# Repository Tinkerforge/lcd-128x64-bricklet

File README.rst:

LCD 128x64 Bricklet
===================

This repository contains the firmware source code and the hardware design
files. The documentation generator configs can be found at
https://github.com/Tinkerforge/generators

Repository Content
------------------

software/:
 * examples/: Examples for all supported languages
 * build/: Compiled files
 * src/: Source code of firmware
 * Makefile: Makefile to build project

hardware/:
 * Contains KiCad project files and additionally schematics as PDF

datasheets/:
 * Contains datasheets for sensors and complex ICs that are used

Hardware
--------

The hardware is designed with the open source EDA Suite KiCad
(http://www.kicad.org). Before you are able to open the files,
you have to install the Tinkerforge kicad-libraries
(https://github.com/Tinkerforge/kicad-libraries). You can either clone
them directly in hardware/ or clone them in a separate folder and
symlink them into hardware/
(ln -s kicad_path/kicad-libraries project_path/hardware). After that you
can open the .pro file in hardware/ with KiCad and from there view and
modify the schematics and the PCB layout.

Software
--------

If you want to do your own Brick/Bricklet firmware development we highly
recommend that you use our build environment setup script and read the
tutorial (https://www.tinkerforge.com/en/doc/Tutorials/Tutorial_Build_Environment/Tutorial.html).

To compile the C code we recommend you to install the newest GNU Arm Embedded
Toolchain (https://launchpad.net/gcc-arm-embedded/+download).
You also need to install bricklib2 (https://github.com/Tinkerforge/bricklib2).

You can either clone it directly in software/src/ or clone it in a
separate folder and symlink it into software/src/
(ln -s bricklib_path/bricklib2 project_path/software/src/). Finally make sure to
have CMake installed (http://www.cmake.org/cmake/resources/software.html).

After that you can build the firmware by invoking make in software/.
The firmware (.zbin) can then be found in software/build/ and uploaded
with brickv (click button "Flashing" on start screen).

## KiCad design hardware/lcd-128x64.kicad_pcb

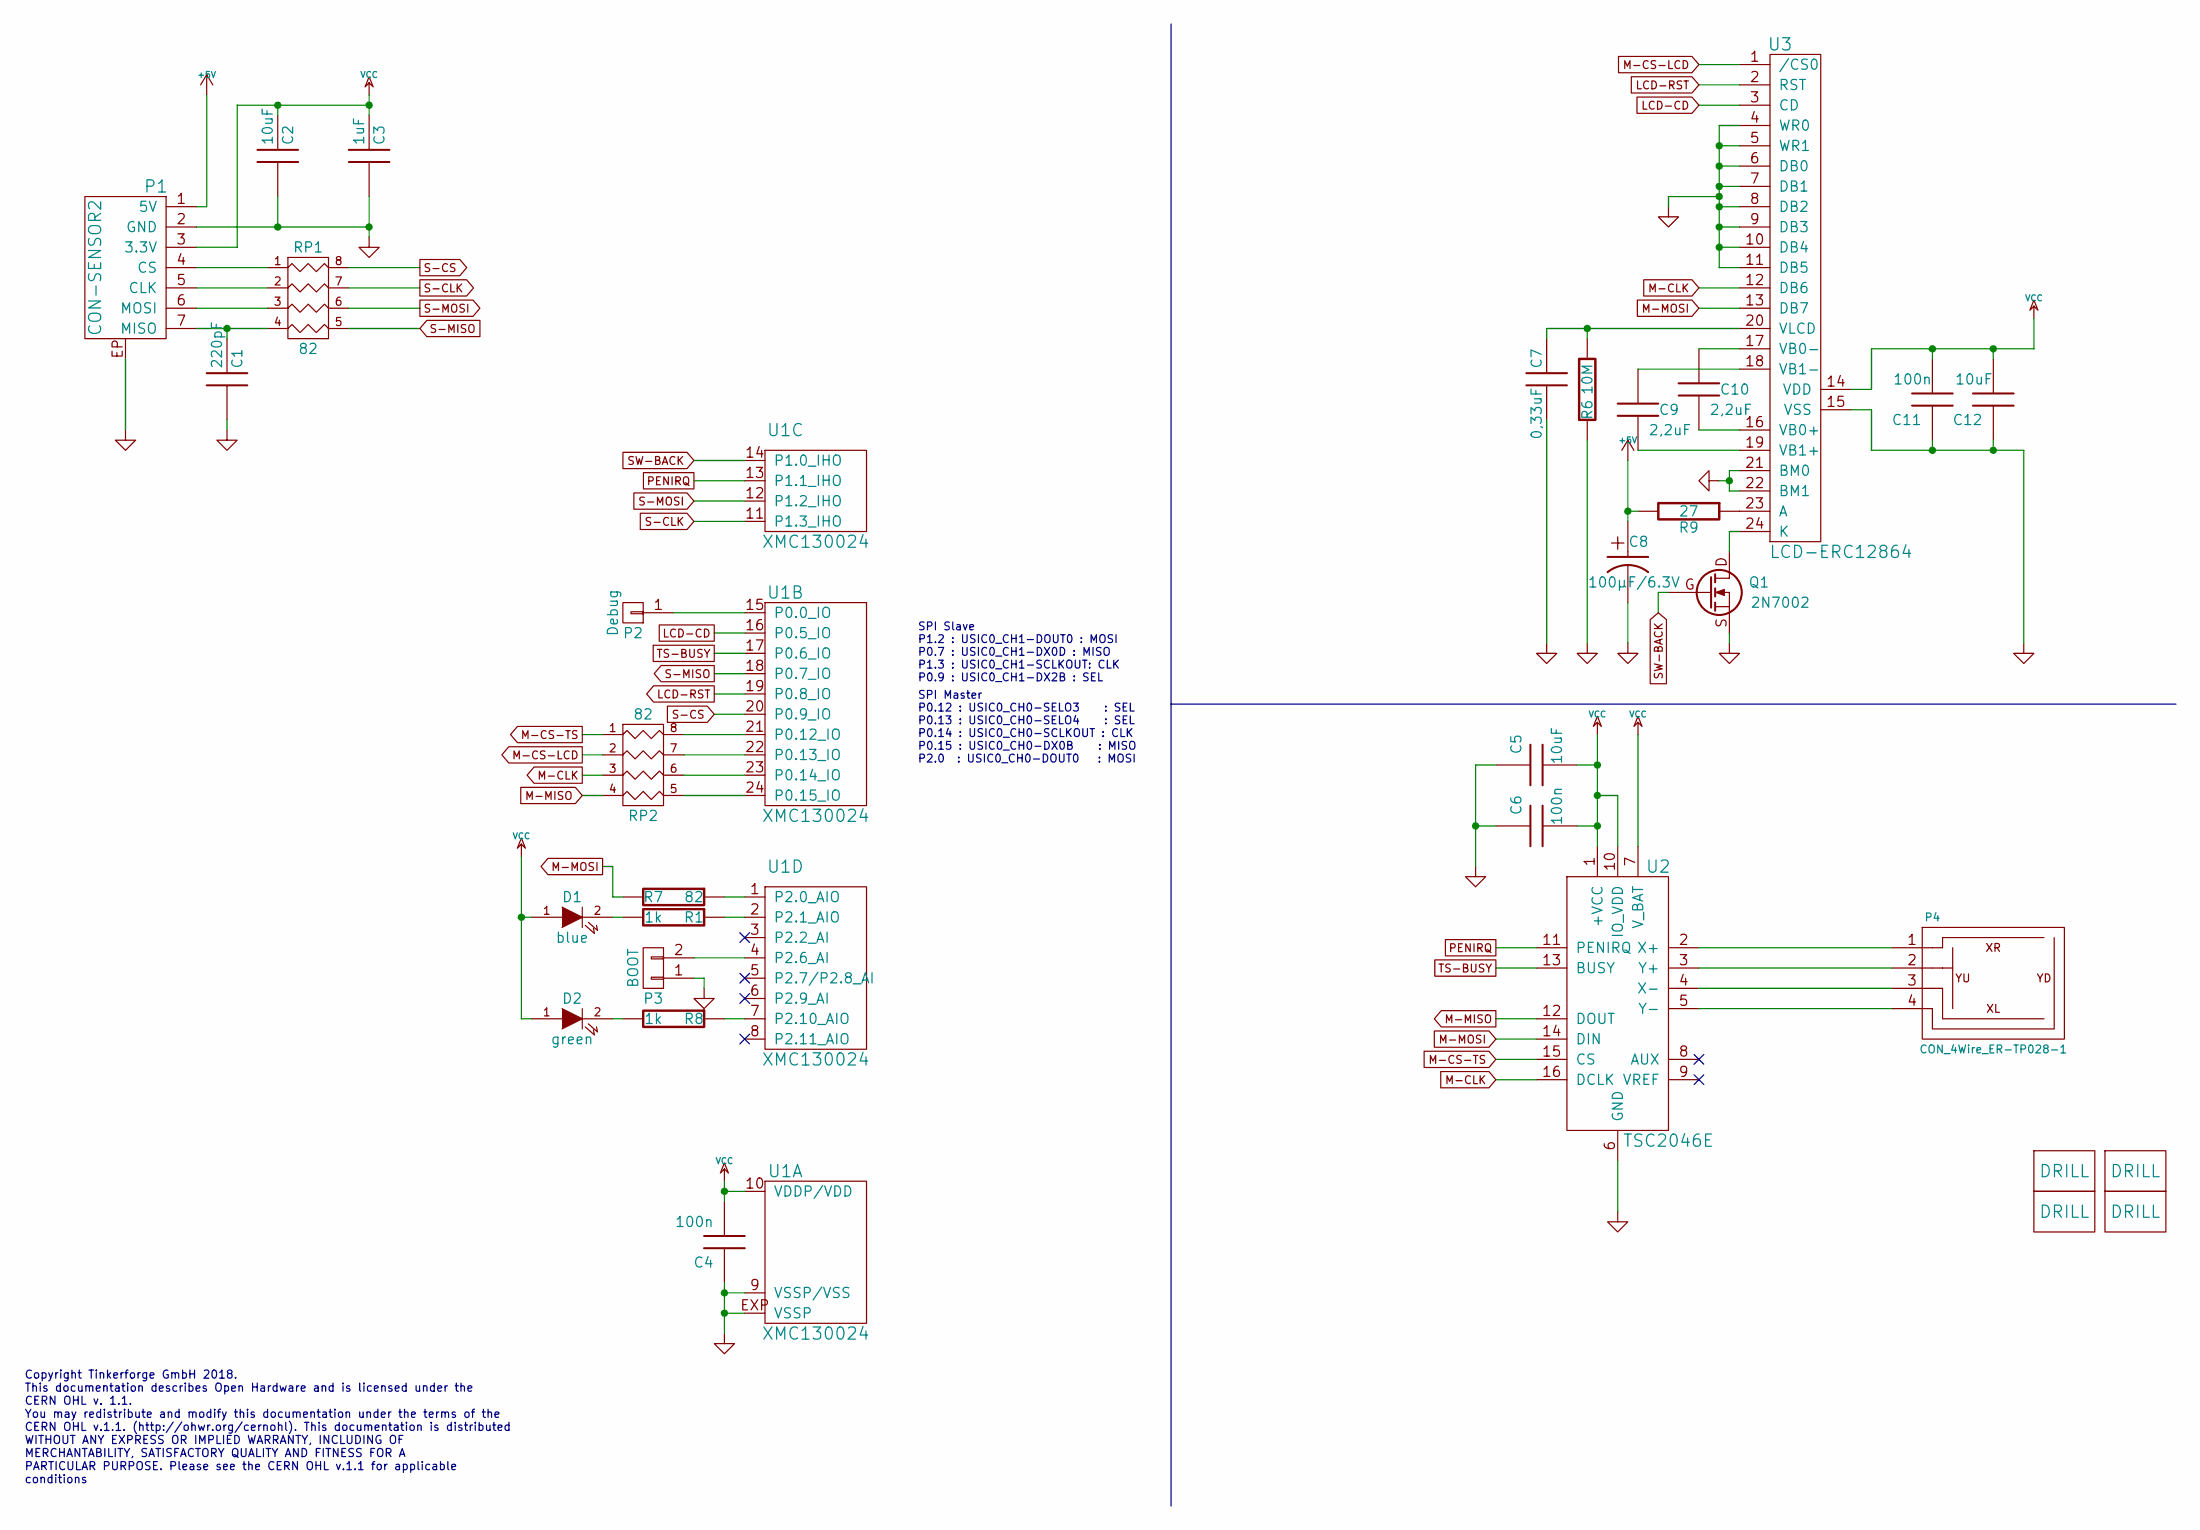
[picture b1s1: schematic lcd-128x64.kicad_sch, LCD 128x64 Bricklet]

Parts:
C1: 220pF; C0402F
C2, C5, C12: 10uF; C0805
C3: 1uF; C0603F
C4, C6, C11: 100n; C0603F
C7: 0,33uF; R0603F
C8: 100µF/6.3V; 3528-21
C9, C10: 2,2uF; C0603F
D1: blue; D0603E
D2: green; D0603E
P1: CON-SENSOR2
P2: Debug; DEBUG_PAD
P3: BOOT; SolderJumper
P4: CON_4Wire_ER-TP028-1; ER-CON04HB-2
Q1: 2N7002; SOT23GDS
R1, R8: 1k; R0603F
R6: 10M; R0603F
R7: 82; R0402F
R9: 27; R1206
RP1, RP2: 82; 4X0402
U1: XMC130024; QFN24-4x4mm-0.5mm
U2: TSC2046E; TSSOP16
U3: LCD-ERC12864; ERC12864-655_128x64
U4, U5, U6, U7: DRILL; DRILL_NP

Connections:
+5V: C8.1, P1.1 (5V), R9.2
GND: C1.2, C2.2, C3.2, C4.1, C5.1, C6.1, C7.2, C8.2, C11.1, C12.1, P1.2 (GND), P1.EP, P3.1, Q1.S, R6.2, U1.9 (VSSP/VSS), U1.EXP (VSSP), U2.6 (GND), U3.4 (WR0), U3.5 (WR1), U3.6 (DB0), U3.7 (DB1), U3.8 (DB2), U3.9 (DB3), U3.10 (DB4), U3.11 (DB5), U3.15 (VSS), U3.21 (BM0), U3.22 (BM1)
LCD-CD: U1.16 (P0.5_IO), U3.3 (CD)
LCD-RST: U1.19 (P0.8_IO), U3.2 (RST)
M-CLK: RP2.3, U2.16 (DCLK), U3.12 (DB6)
M-CS-LCD: RP2.2, U3.1 (/CS0)
M-CS-TS: RP2.1, U2.15 (CS)
M-MISO: RP2.4, U2.12 (DOUT)
M-MOSI: R7.2, U2.14 (DIN), U3.13 (DB7)
unnamed: C1.1, P1.7 (MISO), RP1.4
unnamed: C7.1, R6.1, U3.20 (VLCD)
unnamed: C9.1, U3.18 (VB1-)
unnamed: C9.2, U3.19 (VB1+)
unnamed: C10.1, U3.17 (VB0-)
unnamed: C10.2, U3.16 (VB0+)
unnamed: D1.2 (K), R1.2
unnamed: D2.2 (K), R8.2
unnamed: P1.4 (CS), RP1.1
unnamed: P1.5 (CLK), RP1.2
unnamed: P1.6 (MOSI), RP1.3
unnamed: P2.1, U1.15 (P0.0_IO)
unnamed: P3.2, U1.4 (P2.6_AI)
unnamed: P4.1, U2.2 (X+)
unnamed: P4.2, U2.3 (Y+)
unnamed: P4.3, U2.4 (X-)
unnamed: P4.4, U2.5 (Y-)
unnamed: Q1.D, U3.24 (K)
unnamed: R1.1, U1.2 (P2.1_AIO)
unnamed: R7.1, U1.1 (P2.0_AIO)
unnamed: R8.1, U1.7 (P2.10_AIO)
unnamed: R9.1, U3.23 (A)
unnamed: RP2.5 (R4), U1.24 (P0.15_IO)
unnamed: RP2.6 (R3), U1.23 (P0.14_IO)
unnamed: RP2.7 (R2), U1.22 (P0.13_IO)
unnamed: RP2.8 (R1), U1.21 (P0.12_IO)
PENIRQ: U1.13 (P1.1_IHO), U2.11 (PENIRQ)
S-CLK: RP1.7 (R2), U1.11 (P1.3_IHO)
S-CS: RP1.8 (R1), U1.20 (P0.9_IO)
S-MISO: RP1.5 (R4), U1.18 (P0.7_IO)
S-MOSI: RP1.6 (R3), U1.12 (P1.2_IHO)
SW-BACK: Q1.G, U1.14 (P1.0_IHO)
TS-BUSY: U1.17 (P0.6_IO), U2.13 (BUSY)
VCC: C2.1, C3.1, C4.2, C5.2, C6.2, C11.2, C12.2, D1.1 (A), D2.1 (A), P1.3 (3.3V), U1.10 (VDDP/VDD), U2.1 (+VCC), U2.7 (V_BAT), U2.10 (IO_VDD), U3.14 (VDD)

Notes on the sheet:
SPI Slave P1.2 : USIC0_CH1-DOUT0 : MOSI P0.7 : USIC0_CH1-DX0D : MISO P1.3 : USIC0_CH1-SCLKOUT: CLK P0.9 : USIC0_CH1-DX2B : SEL
SPI Master P0.12 : USIC0_CH0-SELO3 : SEL P0.13 : USIC0_CH0-SELO4 : SEL P0.14 : USIC0_CH0-SCLKOUT : CLK P0.15 : USIC0_CH0-DX0B : MISO P2.0 : USIC0_CH0-DOUT0 : MOSI
Copyright Tinkerforge GmbH 2018. This documentation describes Open Hardware and is licensed under the CERN OHL v. 1.1. You may redistribute and modify this documentation under the terms of the CERN OHL v.1.1. (http://ohwr.org/cernohl). This documentation is distributed WITHOUT ANY EXPRESS OR IMPLIE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

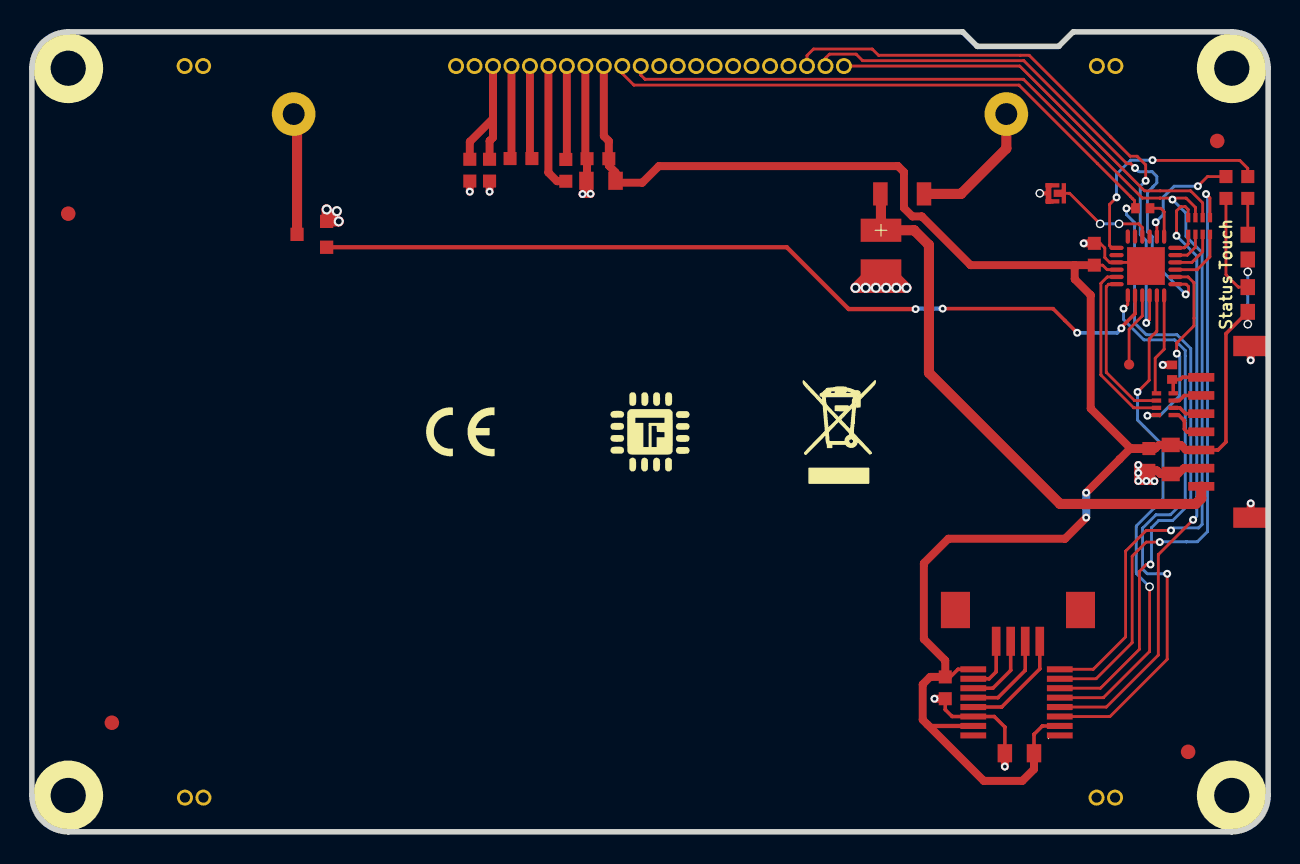
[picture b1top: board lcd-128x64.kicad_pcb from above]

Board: 2 copper layers, 85.0 x 55.0 mm, 39 parts (1 on the bottom side), 43 nets.

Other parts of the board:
Fiducial_Mark: VAL**; Fiducial_Mark
Fiducial_Mark#2, Fiducial_Mark#3, Fiducial_Mark#4: VAL**; Fiducial_Mark
VAL: WEEE_7mm
VAL#2: CE_5mm

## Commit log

2017-12-04 Add datasheets
2017-12-04 Add initial schematic
2017-12-04 Add touch screen controller
2017-12-04 Add connection between touchscreen and XMC
2017-12-04 add interfacing document
2017-12-04 * change 0402 parts to 0603 * change SPI slave an master interfaces
2017-12-05 Annotate components and minor adjustments
2017-12-05 Assign footprints
2017-12-05 Initial PCB
2017-12-05 Fix footprints C11, U2
2017-12-06 add drawing of touchscreen cable
2017-12-07 Change SPI pins, change LCD interface to write-only
2017-12-07 Change pins from debug and boot pads
2017-12-07 Fix last commit
2017-12-07 Complete routing
2017-12-07 add fiducials, destroy layout
2017-12-07 Add status LED for touch
2017-12-07 Change footprint from 0603F to 0805: C5
2017-12-07 Recover routing
2017-12-07 some small layout improvements
2018-01-04 Change pins P1.3 with P0.8
2018-01-04 Resize touchscreen cable through hole
2018-01-08 Fix filled zone
2018-01-08 Change 2017 to 2018
2018-01-22 Bigger holes for LCD
2018-01-25 Change SPI pins because of flashing failure
2018-02-12 display has to be connected to MOSI (not MISO)
2018-02-12 change lcd128 footprint
2018-02-20 Add .gitignore
2018-02-20 Cleanup KiCad libraries config
    Ensure LibDir=kicad-libraries and LibName1=tinkerforge.
    Remove special library.
2018-03-27 Connect LCD backlight to 5v
2018-03-27 Add firmware
2018-03-27 Add missing automatic draw check
2018-03-28 add vscode directory
2018-03-28 Use current max line/position numbers
2018-03-28 Rename column/row to x/y in API
2018-03-28 Add age to touch/gesture callbacks
2018-04-04 Add support for ReadPixels API
2018-04-04 Add new layout (tbc)
2018-04-04 Add simple tests
2018-04-06 Add new layout
2018-04-06 Minor layout adjustments
2018-05-07 hardware changes
    * move touchscreen connector +2mm
    * remove unneccssary resistors
    * move led positions and texts
    * swap led connections
2018-05-11 Rename files
2018-06-06 fix text, set origin
2018-06-18 Fix libraries and footprint
2018-06-28 Fix readme
2018-07-11 Add Makefile with docker support
2018-07-11 Remove obsolete generate_makefile scripts
2018-07-11 Update directory structure and build instructions
2018-07-31 Add 3d model (*.FCStd & *.step)
2018-07-31 Add PDF schematic
2018-09-06 Add font render script
2018-09-10 Use dame coordinate system for touch as for LCD
2018-09-10 Better defaults for contrast and backlight
2018-09-10 Add examples
    LabVIEW example missing.
2018-09-11 Add pixel matrix and scribble example for C
2018-09-11 Add comment with compile parameters
2018-09-11 Add pixel matrix example for Delphi
2018-09-12 Add pixel matrix and scribble examples for java
2018-09-12 Add pixel matrix and scribble example for C#
2018-09-12 Add pixel matrix and scribble examples for JavaScript
2018-09-12 fix c+p error
2018-09-12 Add pixel matrix example for MATLAB/Octave
2018-09-12 Add pixel matrix and scribble example for perl
2018-09-12 Add pixel matrix and scribble example for PHP
2018-09-12 Add pixel matrix and scribble examples for Ruby
2018-09-12 Add load image, pixel matrix and scribble examples for Python
2018-09-12 Add pixel matrix example for shell
2018-09-12 Add pixel matrix and scribble example for VB.NET
2018-09-12 Remove bogus return
2018-09-12 Never trigger position callback by pressure of 1
2018-09-12 Add auto-generated touch examples
2018-09-14 examples: Adapt callback config to common style
2018-09-14 vbnet: Fix typo in comment
2018-09-26 Add pressure-max value to touch-gesture
2018-09-26 Add pressure-max parameter to touch examples
2018-09-26 Clamp input values at 12 bit
2018-09-26 Check division by zero and allow for theoretical large negative resistance
2018-09-26 Dont allow impossible high resistances
    If you press onto a big area of the screen at the same time,
    sometimes the touchscreen controller gets confused and returns
    erroneous x/y positions. In this case the calculation of the
    touch resistance is broken and can return impossibly high
    resistances (pressure > 4200). In this case we ignore the touch
    pressure as well as the x/y position.
2018-10-02 Add BOOTLOADER_FIX_POINTER_END define
2018-10-04 Add rev to changelog
2018-10-16 Remove in-development marker
2018-10-23 fix footprint, remove silkscreen lines
2018-10-31 increase silkscreen text size to 0.8mm
2018-11-06 Add rust examples
2018-11-07 rust: Accept host names for ip connection, fix naming inconsistencies
2018-11-07 rust: Rename callback receivers.
2018-11-13 specify resistor according to production
2018-11-14 Fix touch position sanity check
2018-11-19 Make clear-display obey the automatic-draw config
2018-11-19 Update changelog
2018-11-19 Add commit ref
2018-11-20 Add first GUI elements (button and slider)
2018-11-20 Read actual spi data level instead of always 8
    There is some race condition that somtimes results in a
    false-positive read with the old code. I have not yet actually
    figured out why this happens, this needs more work in the future,
    maybe there is a bug somewhere.
    For now this change fixes the race condition.
2018-11-20 Change slider look
    Remove the bounding box to make them look more like sliders
2018-11-20 Add color parameter to all primitive drawing functions
2018-11-20 Use common redraw function for whole gui
2018-11-21 Set PWM period to 99
    If the PWM period is set to 100, a compare value of 100 results in an
    unintended duty cycle of 1%, with period=99 and compare=100 it works
    properly.
2018-11-21 Add preliminarly changelog entry for 2.0.2
2018-11-21 Add API and implementation for tab-GUI elements
2018-11-22 Use CIE 1931 lookup-table for proper backlight intensity
2018-11-22 Add CIE 1931 hint to changelog
2018-11-22 Add Graph GUI API and implementation
2018-11-22 Add Remove All Gui API and implementation
2018-11-22 Split display buffer into user/gui buffer
    This way the gui can always stay consistent independend of the gui
    and the user can use double buffering while the gui has
    interactive elements at the same time
2018-11-22 Add special handling for GUI remove with index=255
2018-11-22 Update tabs if current tab is changed
2018-11-22 Add support for line and bar graph
2018-11-22 Add tab icon support
2018-11-23 Assume tab is clicked when button in unpressed
2018-11-23 Don't interprete swipe gesture for tab if slider is used
2018-11-23 Use memcpy for bit-array
2018-11-23 Use 12 buttons and 6 sliders
2018-11-23 Const correctness
2018-11-23 Add basic drawing functions
2018-11-23 Add more fonts
    The fonts are generated as multiples in x/y
    from the original 6x8 font
2018-11-26 Add missing sym-lib-table
2018-11-26 Do gui touch check only every fifth loop.
2018-11-26 Fix Status/Touch LED mixup
2018-11-26 Add Set/GetTouchLEDConfig API
2018-11-26 Rename tab current to tab selected
2018-11-28 Add GUI examples
2018-11-28 Increase version to 2.0.2
2018-11-28 Add 2.0.2 ref to changelog
2018-11-28 Fix off-by-one in GUI graph height calcultion
2018-11-28 Fix bug in GUI remove functions
2018-11-28 Add ref for 2.0.3
2018-11-29 Fix wrong initialization of touch LED
2018-11-29 Add ref for version 2.0.4
2018-11-29 Make sure display is updated on GUI remove-event
2018-12-06 Set tab selected back to -1 if tabs are removed
2018-12-14 Add go examples.
2018-12-18 go: Change import path.
2018-12-18 go: Change import path again.
2018-12-20 Add GUI examples.
2018-12-20 rust: Reformat examples.
2019-01-04 Fix off-by-one in button and slider bounding box check
2019-01-04 Add 2.0.6 rev
2019-01-24 mqtt: Add examples.
2019-01-24 mqtt: Fix example header.
2019-01-24 mqtt: Remove executable bit in example permissions.
2019-01-24 go: Minor example fixes.
2019-01-24 mqtt: Minor example fixes.
2019-01-29 c: Fix stream length parameter in GUI example.
2019-03-28 mqtt: Fix whitespace.
2019-03-28 c: Examples: Pre-declare array used as parameter.
2019-05-14 Update rust examples.
2019-05-28 Improve SPI IRQ performance
    Use local pointer to save the time for accessing the struct
2019-05-29 Increase version for new release (changes in bricklib2)
2019-08-13 Add updated font editor
2019-08-22 c: Adapt to bindings changes
2019-08-22 examples: Fix typos in comments
2019-11-18 Don't draw empty tabs if less than 3 are active.
2020-01-13 examples: Use python3 input instead of python2 raw_input.
2020-01-13 examples: mqtt: Remove trailing whitespace.
2020-01-14 examples: Use python3 input by default.
2020-02-26 examples: Update "Change UID" comment style
2020-02-26 examples: Whitespace
2020-03-16 Whitespace
2020-04-03 Add openHAB examples.
2020-04-07 examples: rust: Always block when calling bindings functions.
2020-04-20 Return _EMPTY instead of _NEW_MESSAGE if function has no response data.
    If _NEW_MESSAGE is returned, remove_gui_tab will return the tab to be
    removed if it is not 255. The bindings then raise errors because they
    expect an empty response packet.
2020-04-20 Update changelog and version
2020-04-20 Add commit ref to changelog
2020-04-20 Fix typo in changelog
2020-06-05 Improve draw performance.
    The display_(mask_)write buffer is now refreshed byte-wise instead of
    bit-wise.
    This improves the draw speed as well as the responsiveness to
    SPITFP packets.
2020-06-05 Add commit ref to changelog.
2020-08-19 Add uc examples.
2020-08-25 uc: Fix whitespace
2020-08-27 uc: Fix warnings.
2020-08-31 uc: Use fixed-with placeholders in format strings.
2020-09-02 uc: Add example driver note.
2021-06-15 Make sure position_value_has_to_change=False works with touch_pressure=1
2021-06-15 Add ref
2021-10-25 Update KiCad link
    https://www.kicad.org/blog/2021/10/Avoid-links-to-former-kicad-domain/
2022-03-07 Add code page 437 hint
2022-04-19 examples: uc: Rename TF_HalContext to TF_HAL.
2022-04-27 uc: Adapt to bindings changes
2022-07-06 Add license files.
2023-06-20 move to new kicad version
2024-02-23 vbnet: Fix for loops
2025-10-04 Fix compatibility with new Docker build image (GCC 14.2.1)

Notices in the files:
hardware/lcd-128x64.kicad_pcb:
Licensed under CERN OHL v.1.1
Copyright (©) 2018, L.Lauer
